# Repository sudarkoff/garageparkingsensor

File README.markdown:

# Parking Sensor

Garage Parking Sensor is a gizmo that helps you park your car the perfect distance from the wall every time. It can also optionally serve as a presence sensor.

## Usage

To save the sweet spot, using whatever means necessary - your spouse, a tennis ball suspended from the ceiling, a bunch of mirrors with lasers - park the car the disared distance away from the wall where the sensor is mounted (for best results, aim the sensor at your car's bumper). Once satisfied with the location of your car, push the Save button on the gizmo taking care not to interfere with the ultrasound beam between the sensor and the car. The distance will be saved into the non-volatile memory (meaning, it will survive the reboot or the loss of power).

To park in the same perfect spot, drive *slowly* until the red LED starts to blink, then stop. The LEDs of the gizmo indicate the relative distance to your perfect spot. The first three yellow LEDs cover the range from approximately 3 meters (max detectable distance) to within about 20% of the target spot. Two green LEDs are for the 20% to 5% range. Finally, the red LED indicates that you're less than 5% away from your target spot (we're talking millimeters at this point). In practical terms, the sensor forces you to slow down fast and puts you within your target zone with the precision of a sharp shooter. It is *very* accurate!

## Schematics

The circuit is Arduino-compatible. That means it uses the ATmega microprocessor unit with the Arduino bootloader. However, there is no USB on board, the only way to communicate with the board is to use an FTDI breakout board similar to [this](https://www.sparkfun.com/products/9716). The ultrasound sensor used ("PING)))") is probably the most expensive component of this gizmo (I bought mine for about $30). I used [Eagle](http://www.cadsoftusa.com/) to design and draw the schematics and the PCB.

## Firmware

Firmware is Arduino-based, so you'll have to install and know how to use the Arduino software in order to tinker and upload the firmware to the board.

To be continued...

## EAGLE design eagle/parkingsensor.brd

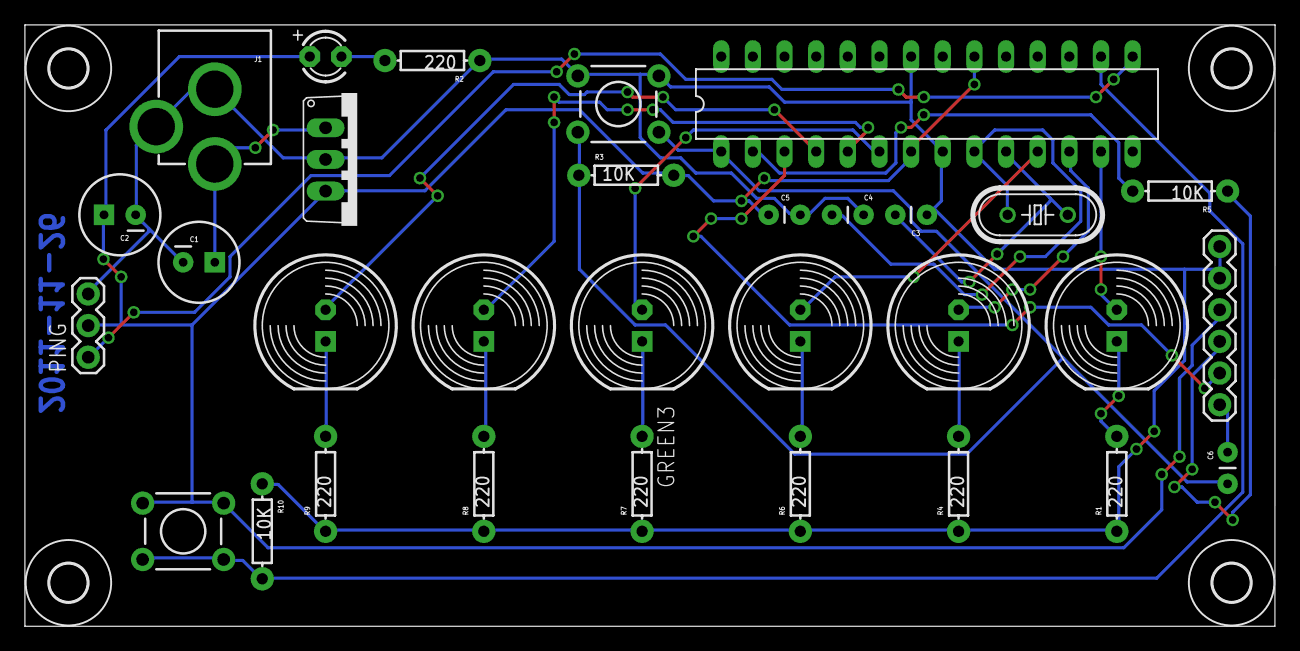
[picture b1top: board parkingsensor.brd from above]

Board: 2 copper layers, 100.3 x 48.3 mm, 35 parts (0 on the bottom side), 25 nets.

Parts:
C1: 100uF/25V; CPOL-RADIAL-100UF-25V
C2: 10uF/10V; CPOL-RADIAL-100UF-25V
C3, C4: 22pF; CAP-PTH-SMALL
C5, C6: 0.1uF; CAP-PTH-SMALL
GREEN1, GREEN2, GREEN3: LED10MM
IC1: 7805TV; TO220V
J1: POWER_JACKPTH; POWER_JACK_PTH
JP1: XBee/Program; 1X06
LED1: POWER; LED3MM
PING: 1X03
Q1: 16MHz; HC49/S
R1, R2, R4, R6, R7, R8, R9: 220; AXIAL-0.3
R3, R5, R10: 10K; AXIAL-0.3
RED1: LED10MM
RESET: TACTILE-PTH
STORE: TACTILE-PTH
U$1, U$2, U$3, U$4: MOUNTINGHOLE_3.0
YELLOW1, YELLOW2: LED10MM
ZIC1: ATMEGA328; DIL28-3

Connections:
+5V: C2.1, C5.2, IC1.3, JP1.4, LED1.A, PING.2, R3.P$2, STORE.3, STORE.4, ZIC1.7, ZIC1.20
+12V: C1.1, IC1.1, J1.PWR
DIST: PING.1, ZIC1.15
DTR: C6.1, JP1.1
GND: C1.2, C2.2, C3.1, C4.1, C5.1, IC1.2, J1.GND, J1.GNDBREAK, JP1.5, JP1.6, PING.3, R1.P$1, R2.P$1, R4.P$1, R6.P$1, R7.P$1, R8.P$1, R9.P$1, R10.P$1, RESET.1, RESET.2, ZIC1.8, ZIC1.22
GREEN1: GREEN1.A, ZIC1.4
GREEN2: GREEN2.A, ZIC1.5
GREEN3: GREEN3.A, ZIC1.6
unnamed: R1.P$2, RED1.K
unnamed: R4.P$2, YELLOW2.K
unnamed: R6.P$2, YELLOW1.K
unnamed: GREEN3.K, R7.P$2
unnamed: C3.2, Q1.2, ZIC1.10
unnamed: LED1.K, R2.P$2
unnamed: C4.2, Q1.1, ZIC1.9
unnamed: C6.2, R3.P$1, RESET.3, RESET.4, ZIC1.1
unnamed: JP1.3, R5.P$1
unnamed: GREEN2.K, R8.P$2
unnamed: GREEN1.K, R9.P$2
unnamed: R10.P$2, STORE.1, STORE.2, ZIC1.16
RED1: RED1.A, ZIC1.13
RX: R5.P$2, ZIC1.2
TX: JP1.2, ZIC1.3
YELLOW1: YELLOW1.A, ZIC1.11
YELLOW2: YELLOW2.A, ZIC1.12

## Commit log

2014-05-27 Initial version of the Parking Sensor firmware.
2014-05-27 Add README
2014-06-01 Add link to Eagle software.
2014-06-23 Add the schematic and the PCB layout.
2014-06-23 Extracted Usage into its own section.
    ...And changed some wording a bit.
2014-06-23 Add picture
2014-06-23 Replace image with bigger one.
